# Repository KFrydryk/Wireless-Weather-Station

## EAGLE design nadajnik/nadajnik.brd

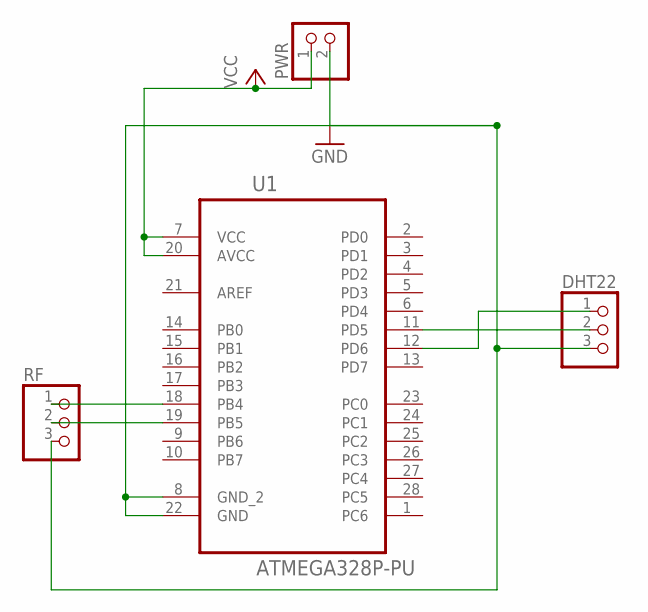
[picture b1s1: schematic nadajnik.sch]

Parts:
DHT22: PINHD-1X3; 1X03
PWR: PINHD-1X2; 1X02
RF: PINHD-1X3; 1X03
U1: ATMEGA328P-PU; DIP254P762X457-28

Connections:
GND: DHT22.3, PWR.2, RF.3, U1.8 (GND_2), U1.22 (GND)
unnamed: DHT22.1, U1.12 (PD6)
unnamed: DHT22.2, U1.11 (PD5)
unnamed: RF.1, U1.18 (PB4)
unnamed: RF.2, U1.19 (PB5)
VCC: PWR.1, U1.7 (VCC), U1.20 (AVCC)

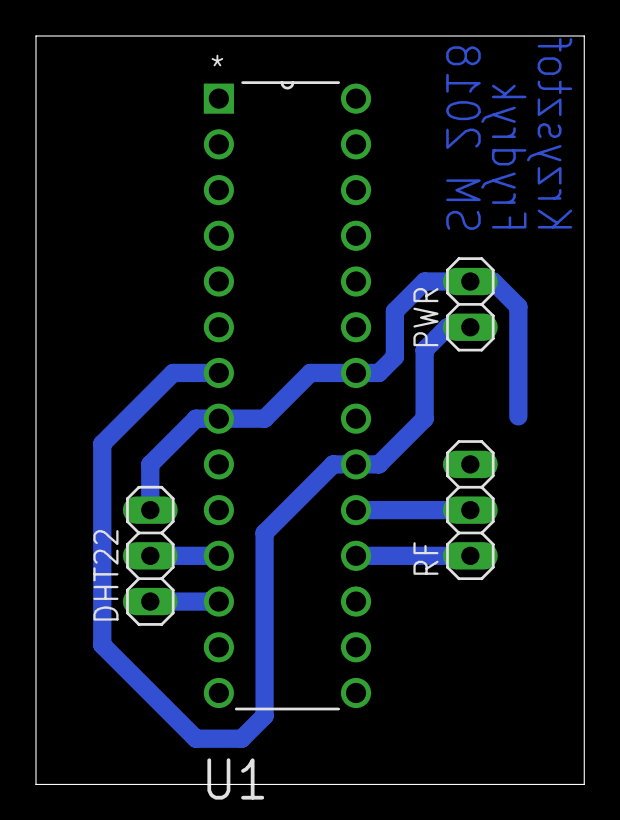
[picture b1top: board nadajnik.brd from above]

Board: 2 copper layers, 30.5 x 41.6 mm, 4 parts (0 on the bottom side), 6 nets.

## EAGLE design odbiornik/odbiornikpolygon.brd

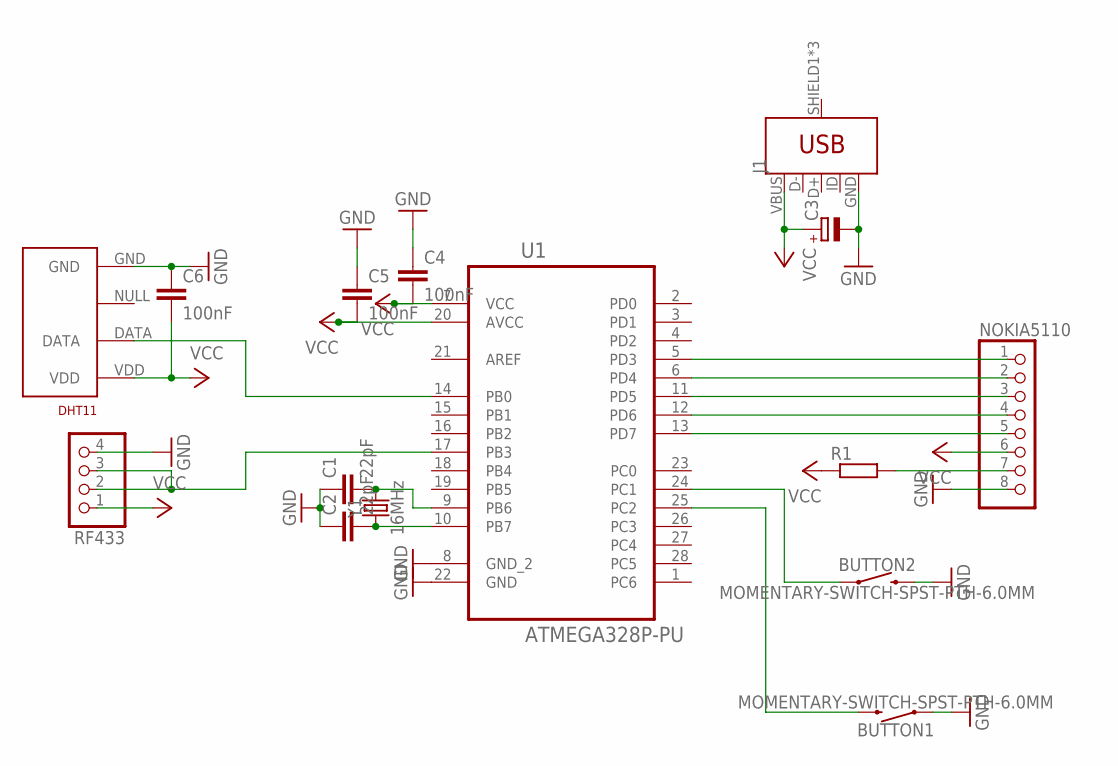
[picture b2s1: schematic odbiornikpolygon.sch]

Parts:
BUTTON1, BUTTON2: MOMENTARY-SWITCH-SPST-PTH-6.0MM; TACTILE_SWITCH_PTH_6.0MM
C1, C2: 22pF; C025-024X044
C3: CPOL-EUE2-5; E2-5
C4, C5, C6: 100nF; C025-030X050
DHT11: RHT03_DHT-22_AM2302; RHT03_DHT-22
J1: USB_MICRO-BREDUCED_PASTE; USB-B-MICRO-SMD_RED_PASTE
NOKIA5110: PINHD-1X8; 1X08
R1: R-EU_0204/7; 0204/7
RF433: PINHD-1X4; 1X04
U1: ATMEGA328P-PU; DIP254P762X457-28
Y1: 16MHz; HC49US

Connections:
BL: NOKIA5110.7, R1.2
CE: NOKIA5110.2, U1.6 (PD4)
CLK: NOKIA5110.5, U1.13 (PD7)
DC: NOKIA5110.3, U1.11 (PD5)
DIN: NOKIA5110.4, U1.12 (PD6)
GND: BUTTON1.1, BUTTON2.3 (2), C1.1, C2.1, C3.-, C4.1, C5.1, C6.1, DHT11.GND, J1.GND, NOKIA5110.8, RF433.4, U1.8 (GND_2), U1.22 (GND)
unnamed: BUTTON1.3 (2), U1.25 (PC2)
unnamed: RF433.2, RF433.3, U1.17 (PB3)
unnamed: DHT11.DATA, U1.14 (PB0)
unnamed: BUTTON2.1, U1.24 (PC1)
unnamed: C1.2, U1.9 (PB6), Y1.2
unnamed: C2.2, U1.10 (PB7), Y1.1
RST: NOKIA5110.1, U1.5 (PD3)
VCC: C3.+, C4.2, C5.2, C6.2, DHT11.VDD, J1.VBUS, NOKIA5110.6, R1.1, RF433.1, U1.7 (VCC), U1.20 (AVCC)

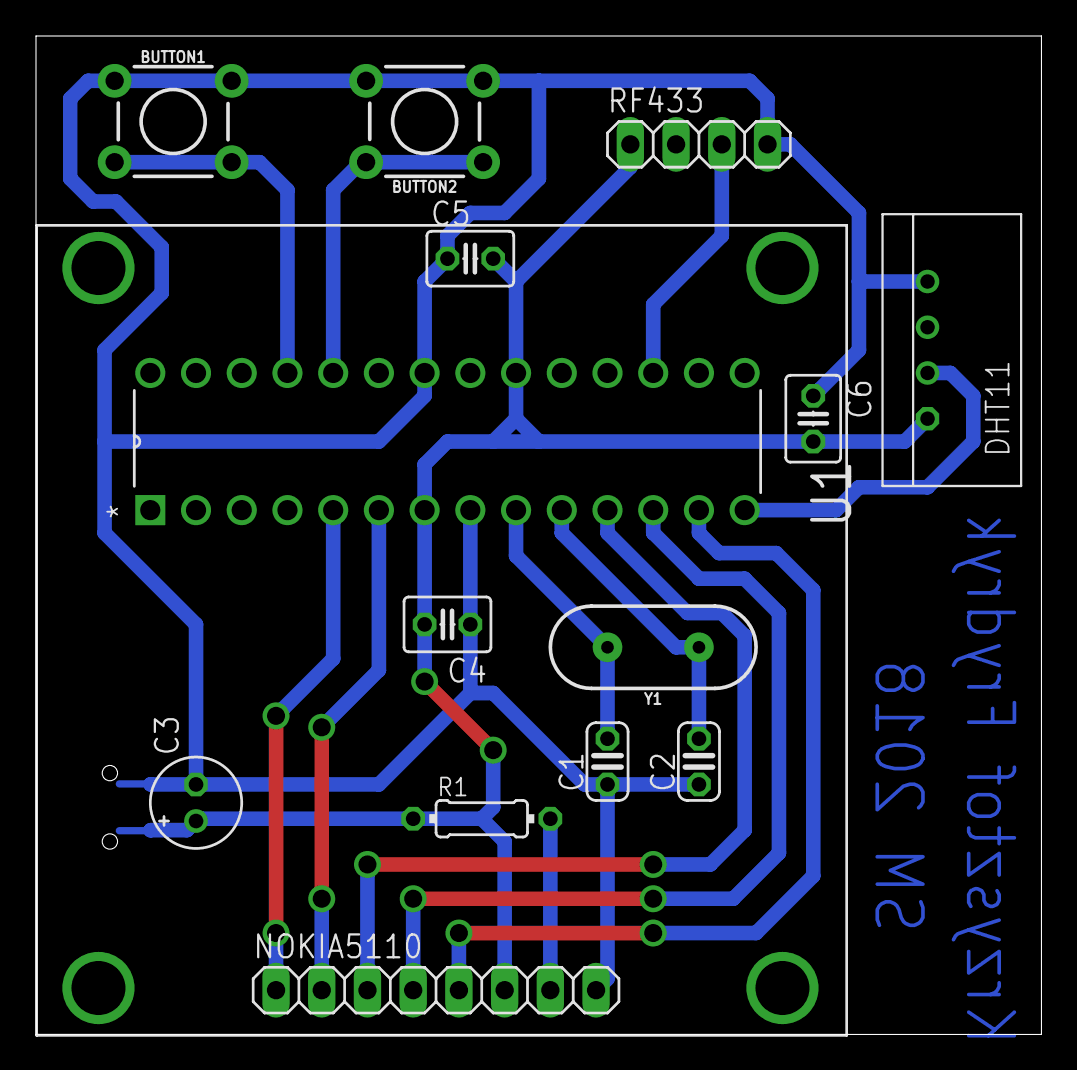
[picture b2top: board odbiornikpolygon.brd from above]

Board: 2 copper layers, 55.9 x 55.5 mm, 15 parts (1 on the bottom side), 14 nets.

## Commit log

2020-04-19 first and last commit - it's a backup
2020-04-19 added Eagle files - still only a backup
2020-05-04 added photos and schematics

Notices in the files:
parts and their libraries:
SparkFun-Connectors: Licensing: Creative Commons ShareAlike 4.0 International - https://creativecommons.org/licenses/by-sa/4.0
